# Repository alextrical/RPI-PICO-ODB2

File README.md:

# RPI-PICO-ODB2
ODB to RPI-PICO to be used with the PiCCANTE Project

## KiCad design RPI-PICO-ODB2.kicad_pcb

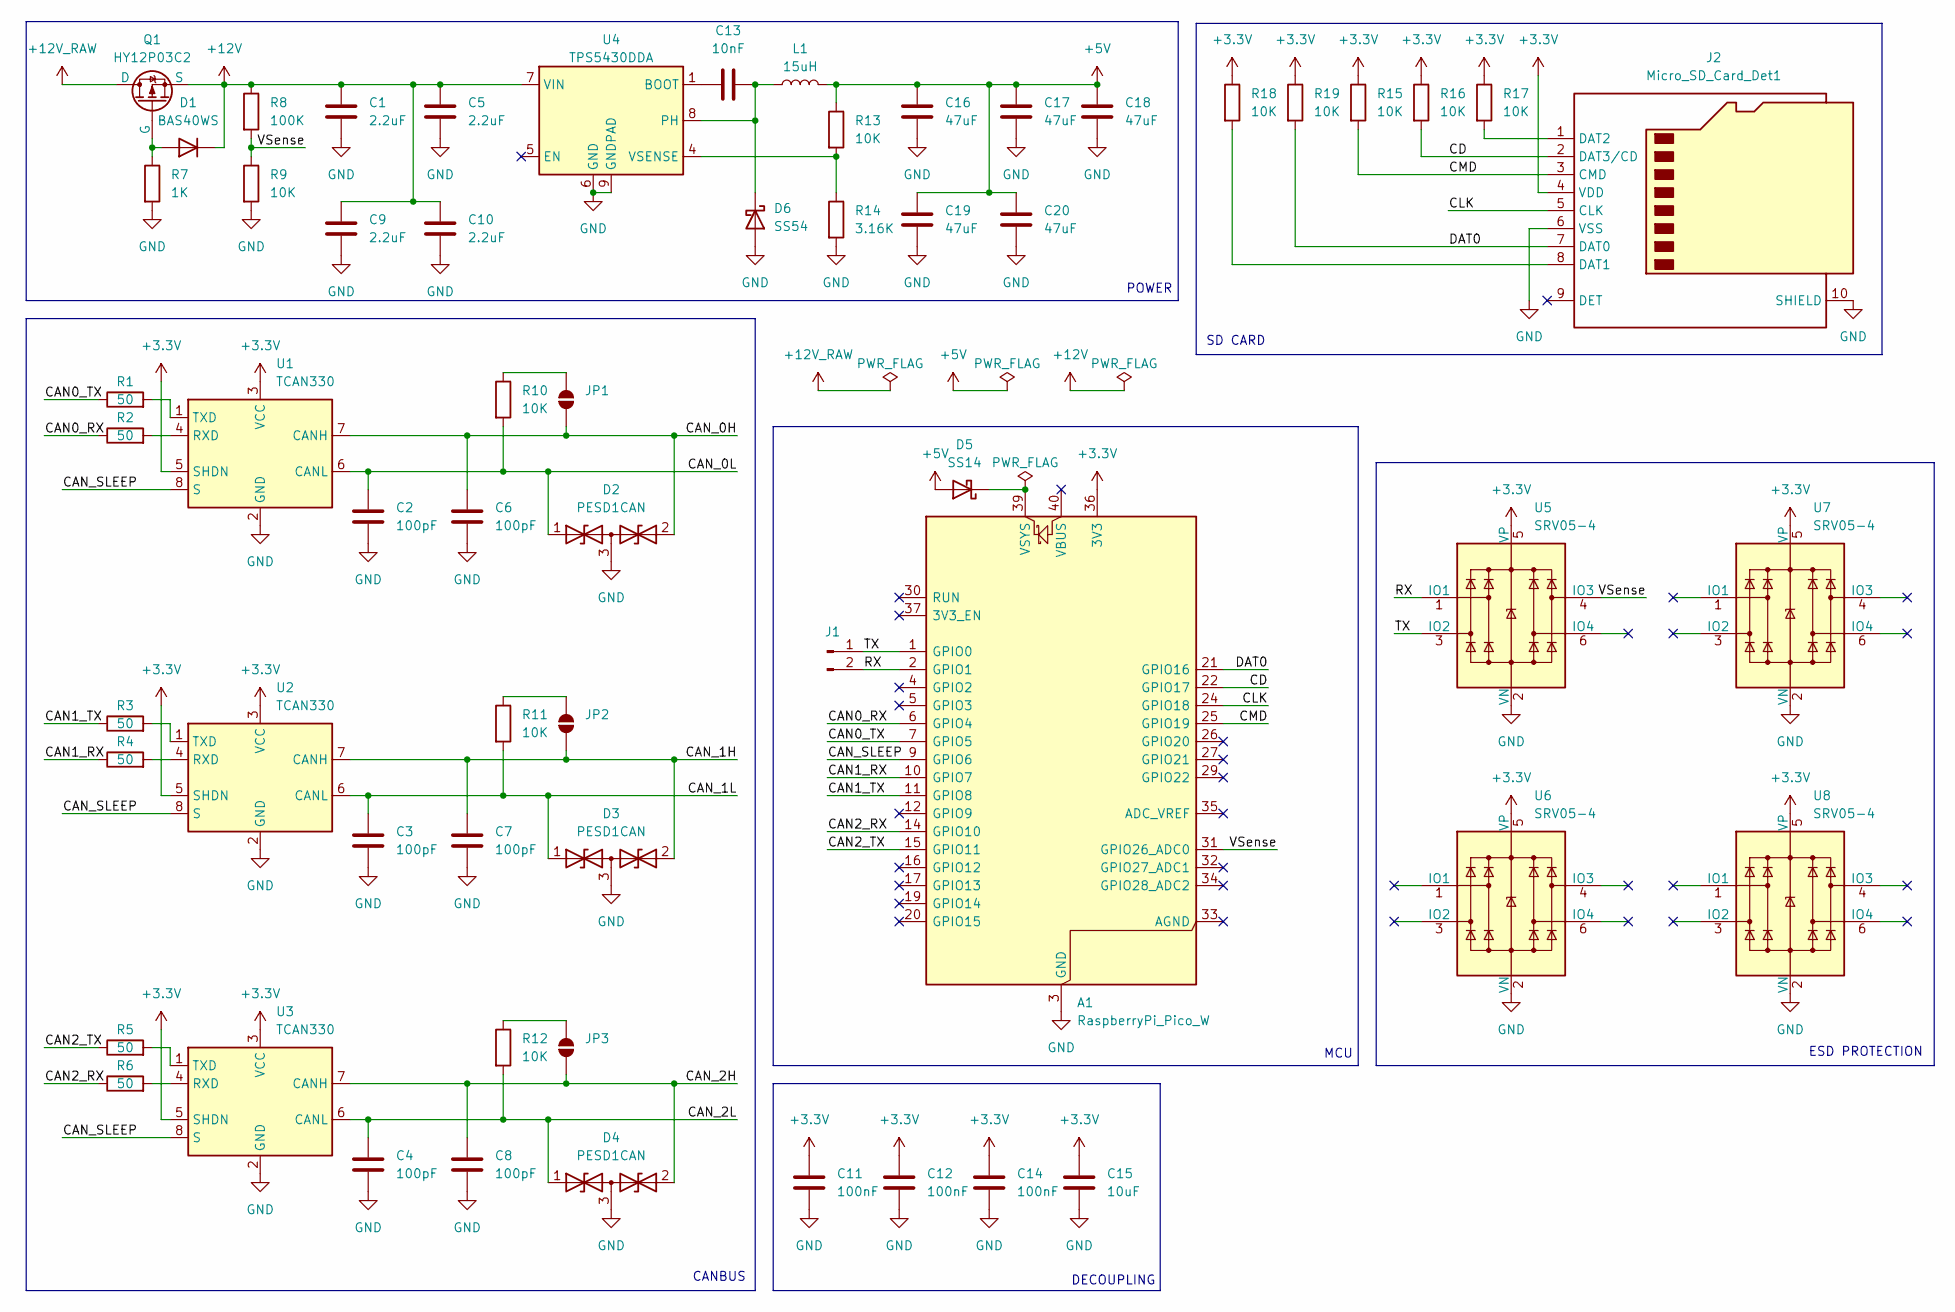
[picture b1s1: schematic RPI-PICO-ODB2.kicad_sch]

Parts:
A1: RaspberryPi_Pico_W; RaspberryPi_Pico_W_SMD_HandSolder
C1, C5, C9, C10: 2.2uF; C_0805_2012Metric
C2, C3, C4, C6, C7, C8: 100pF; C_0402_1005Metric; LCSC C1546
C11, C12, C14: 100nF; C_0402_1005Metric; LCSC C1525
C13: 10nF; C_0402_1005Metric
C15: 10uF; C_0603_1608Metric; LCSC C1525
C16, C17, C18, C19, C20: 47uF; C_0805_2012Metric
D1: BAS40WS; D_SOD-323; LCSC C28646260
D2, D3, D4: PESD1CAN; SOT-23; LCSC C907839
D5: SS14; D_SMA; LCSC C2480
D6: SS54; D_SMA; LCSC C22452
J1: Conn_01x02_Pin; JST_XH_B2B-XH-A_1x02_P2.50mm_Vertical
J2: Micro_SD_Card_Det1; TF-SMD_TF-01A
JP1, JP2, JP3: SolderJumper_2_Open; SolderJumper-2_P1.3mm_Open_RoundedPad1.0x1.5mm
L1: 15uH; L_10.4x10.4_H4.8
Q1: HY12P03C2; AO_DFN-8-1EP_5.55x5.2mm_P1.27mm_EP4.12x4.6mm
R1, R2, R3, R4, R5, R6: 50; R_0402_1005Metric
R7: 1K; R_0402_1005Metric
R8: 100K; R_0402_1005Metric
R9, R10, R11, R12, R13, R15, R16, R17, R18, R19: 10K; R_0402_1005Metric
R14: 3.16K; R_0402_1005Metric
U1, U2, U3: TCAN330; JEITA_SOIC-8_3.9x4.9mm_P1.27mm
U4: TPS5430DDA; TI_SO-PowerPAD-8_ThermalVias
U5, U6, U7, U8: SRV05-4; SOT-23-6

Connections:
+3.3V: A1.36 (3V3), C11.1, C12.1, C14.1, C15.1, J2.4 (VDD), R15.1, R16.1, R17.1, R18.1, R19.1, U1.3 (VCC), U1.5 (SHDN), U2.3 (VCC), U2.5 (SHDN), U3.3 (VCC), U3.5 (SHDN), U5.5 (VP), U6.5 (VP), U7.5 (VP), U8.5 (VP)
+5V: C16.1, C17.1, C18.1, C19.1, C20.1, D5.2 (A), L1.2, R13.1
+12V: C1.1, C5.1, C9.1, C10.1, D1.1 (K), Q1.3 (S), R8.1, U4.7 (VIN)
+12V_RAW: Q1.1 (D)
/CAN0_RX: A1.6 (GPIO4), R2.1
/CAN0_TX: A1.7 (GPIO5), R1.1
/CAN1_RX: A1.10 (GPIO7), R4.1
/CAN1_TX: A1.11 (GPIO8), R3.1
/CAN2_RX: A1.14 (GPIO10), R6.1
/CAN2_TX: A1.15 (GPIO11), R5.1
/CAN_0H: C6.1, D2.2 (A2), JP1.1 (A), U1.7 (CANH)
/CAN_0L: C2.1, D2.1 (A1), R10.2, U1.6 (CANL)
/CAN_1H: C7.1, D3.2 (A2), JP2.1 (A), U2.7 (CANH)
/CAN_1L: C3.1, D3.1 (A1), R11.2, U2.6 (CANL)
/CAN_2H: C8.1, D4.2 (A2), JP3.1 (A), U3.7 (CANH)
/CAN_2L: C4.1, D4.1 (A1), R12.2, U3.6 (CANL)
/CAN_SLEEP: A1.9 (GPIO6), U1.8 (S), U2.8 (S), U3.8 (S)
/CD: A1.22 (GPIO17), J2.2 (DAT3/CD), R16.2
/CLK: A1.24 (GPIO18), J2.5 (CLK)
/CMD: A1.25 (GPIO19), J2.3 (CMD), R15.2
/DAT0: A1.21 (GPIO16), J2.7 (DAT0), R19.2
/RX: A1.2 (GPIO1), J1.2, U5.1 (IO1)
/TX: A1.1 (GPIO0), J1.1, U5.3 (IO2)
/VSense: A1.31 (GPIO26_ADC0), R8.2, R9.1, U5.4 (IO3)
GND: A1.3 (GND), A1.8 (GND), A1.13 (GND), A1.18 (GND), A1.23 (GND), A1.28 (GND), A1.38 (GND), C1.2, C2.2, C3.2, C4.2, C5.2, C6.2, C7.2, C8.2, C9.2, C10.2, C11.2, C12.2, C14.2, C15.2, C16.2, C17.2, C18.2, C19.2, C20.2, D2.3 (common), D3.3 (common), D4.3 (common), D6.2 (A), J2.6 (VSS), J2.10 (SHIELD), R7.2, R9.2, R14.2, U1.2 (GND), U2.2 (GND), U3.2 (GND), U4.6 (GND), U4.9 (GNDPAD), U5.2 (VN), U6.2 (VN), U7.2 (VN), U8.2 (VN)
unnamed: A1.39 (VSYS), D5.1 (K)
unnamed: D1.2 (A), Q1.2 (G), R7.1
unnamed: C13.2, D6.1 (K), L1.1, U4.8 (PH)
unnamed: J2.8 (DAT1), R18.2
unnamed: J2.1 (DAT2), R17.2
unnamed: JP1.2 (B), R10.1
unnamed: JP2.2 (B), R11.1
unnamed: JP3.2 (B), R12.1
unnamed: R2.2, U1.4 (RXD)
unnamed: R1.2, U1.1 (TXD)
unnamed: R4.2, U2.4 (RXD)
unnamed: R3.2, U2.1 (TXD)
unnamed: R6.2, U3.4 (RXD)
unnamed: R5.2, U3.1 (TXD)
unnamed: C13.1, U4.1 (BOOT)
unnamed: R13.2, R14.1, U4.4 (VSENSE)

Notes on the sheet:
ESD PROTECTION
SD CARD
DECOUPLING
MCU
CANBUS
POWER

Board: 2 copper layers, 61 parts (1 on the bottom side), 40 nets, no tracks yet.

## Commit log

2025-12-24 Commit schematic and github actions
2025-12-24 comment out panelize workflow
2025-12-24 Remove submodule pull from workflow
2025-12-24 Auto set Project file name
2025-12-24 Create test-results.log with run results
2025-12-24 test-results.log debug
2025-12-24 Test results log upload
2025-12-24 Test
2025-12-24 Test2
2025-12-24 test 3
2025-12-24 test 4
2025-12-24 test 6
